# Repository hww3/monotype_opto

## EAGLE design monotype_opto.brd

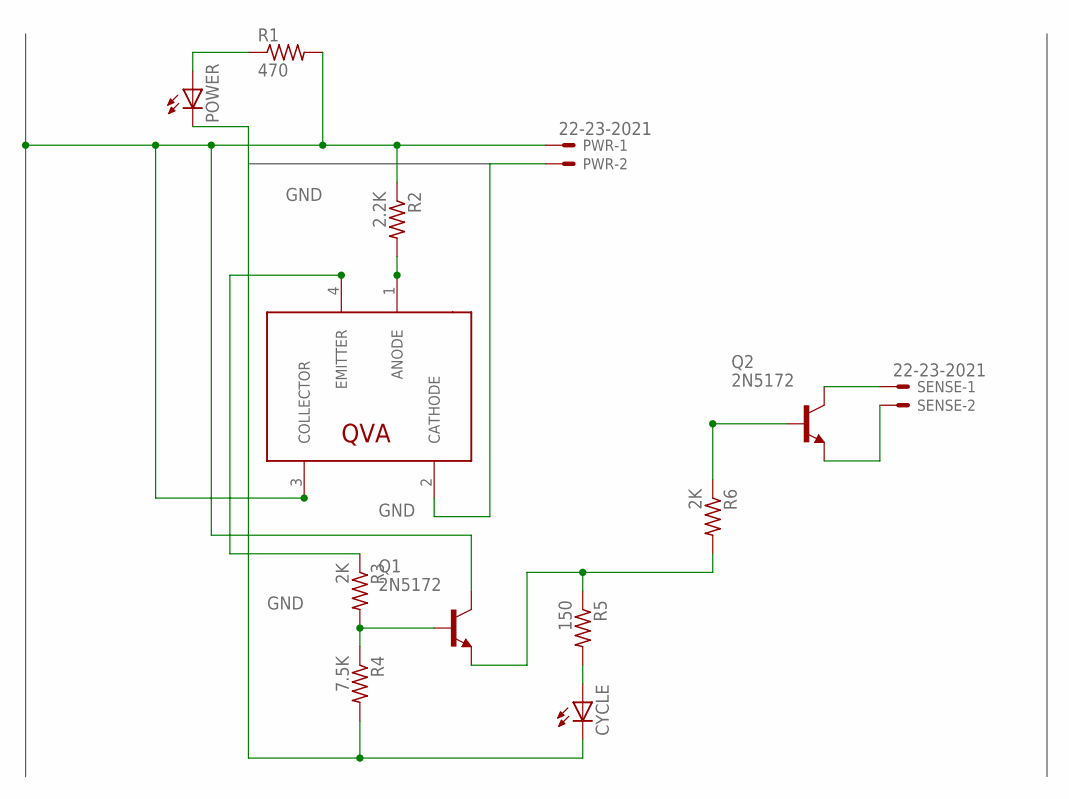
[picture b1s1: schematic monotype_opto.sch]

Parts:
CYCLE: LED3MM
POWER: LED3MM
PWR: 22-23-2021
Q1, Q2: 2N5172; TO92
R1: 470; 0411/12
R2: 2.2K; 0411/12
R3, R6: 2K; 0411/12
R4: 7.5K; 0411/12
R5: 150; 0411/12
SENSE: 22-23-2021
U$1: QVA; QVA11134

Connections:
+12V: PWR.1, Q1.2 (C), R1.2, R2.1, U$1.3 (COLLECTOR)
GND: CYCLE.K (C), POWER.K (C), PWR.2, R4.2, U$1.2 (CATHODE)
unnamed: Q2.1 (B), R6.1
unnamed: Q2.2 (C), SENSE.1
unnamed: Q1.3 (E), R5.1, R6.2
unnamed: POWER.A, R1.1
unnamed: Q2.3 (E), SENSE.2
unnamed: R2.2, U$1.1 (ANODE)
unnamed: CYCLE.A, R5.2
unnamed: Q1.1 (B), R3.2, R4.1
unnamed: R3.1, U$1.4 (EMITTER)

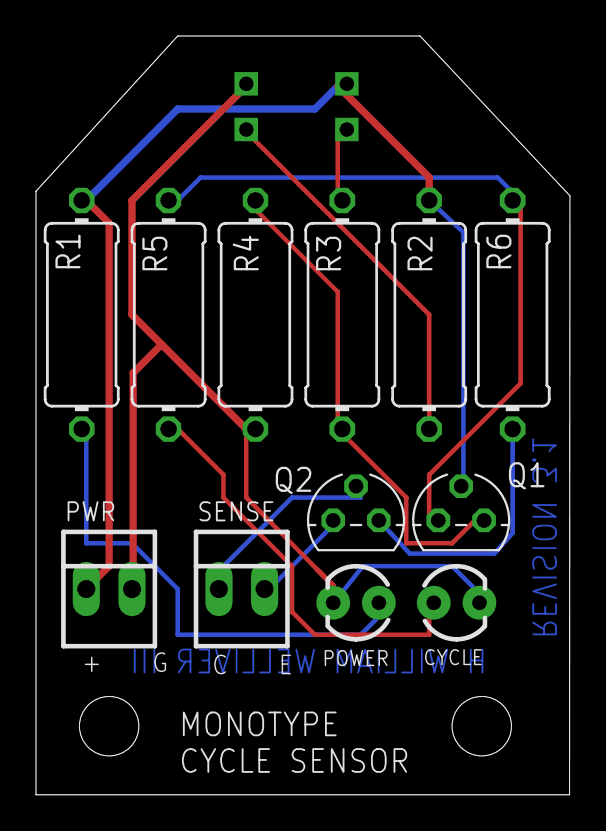
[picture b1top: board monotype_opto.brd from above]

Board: 2 copper layers, 29.7 x 42.2 mm, 15 parts (1 on the bottom side), 11 nets.

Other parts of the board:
U$2, U$3: STAND-OFF

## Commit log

2014-05-13 initial commit of monotype optical sensor board; better late than never.

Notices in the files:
parts and their libraries:
SparkFun: Licensing: CC v3.0 Share-Alike You are welcome to use this library for commercial purposes.
